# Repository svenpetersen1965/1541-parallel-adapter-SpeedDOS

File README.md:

# 1541-parallel-adapter-SpeedDOS
This is a reliable and easy to build parallel User Port Adapter for the Commodore 1541/1541-II for SpeedDOS

The project consists out of a user port module with a 3D printed case, which also includes a RESET button for the C64. 

There are two different VIA adapters for the 1541 and a low profile one for the narrower sapce in the 1541-II.

BOM Values:
* 1541 Adapter (cable included): 4.91€ (28.06.2020)
* 1541-II Adapter (cable included): 3.30€ (10.12.2020)
* User Port Adapter (no case): 4.65€ (28.06.2020)

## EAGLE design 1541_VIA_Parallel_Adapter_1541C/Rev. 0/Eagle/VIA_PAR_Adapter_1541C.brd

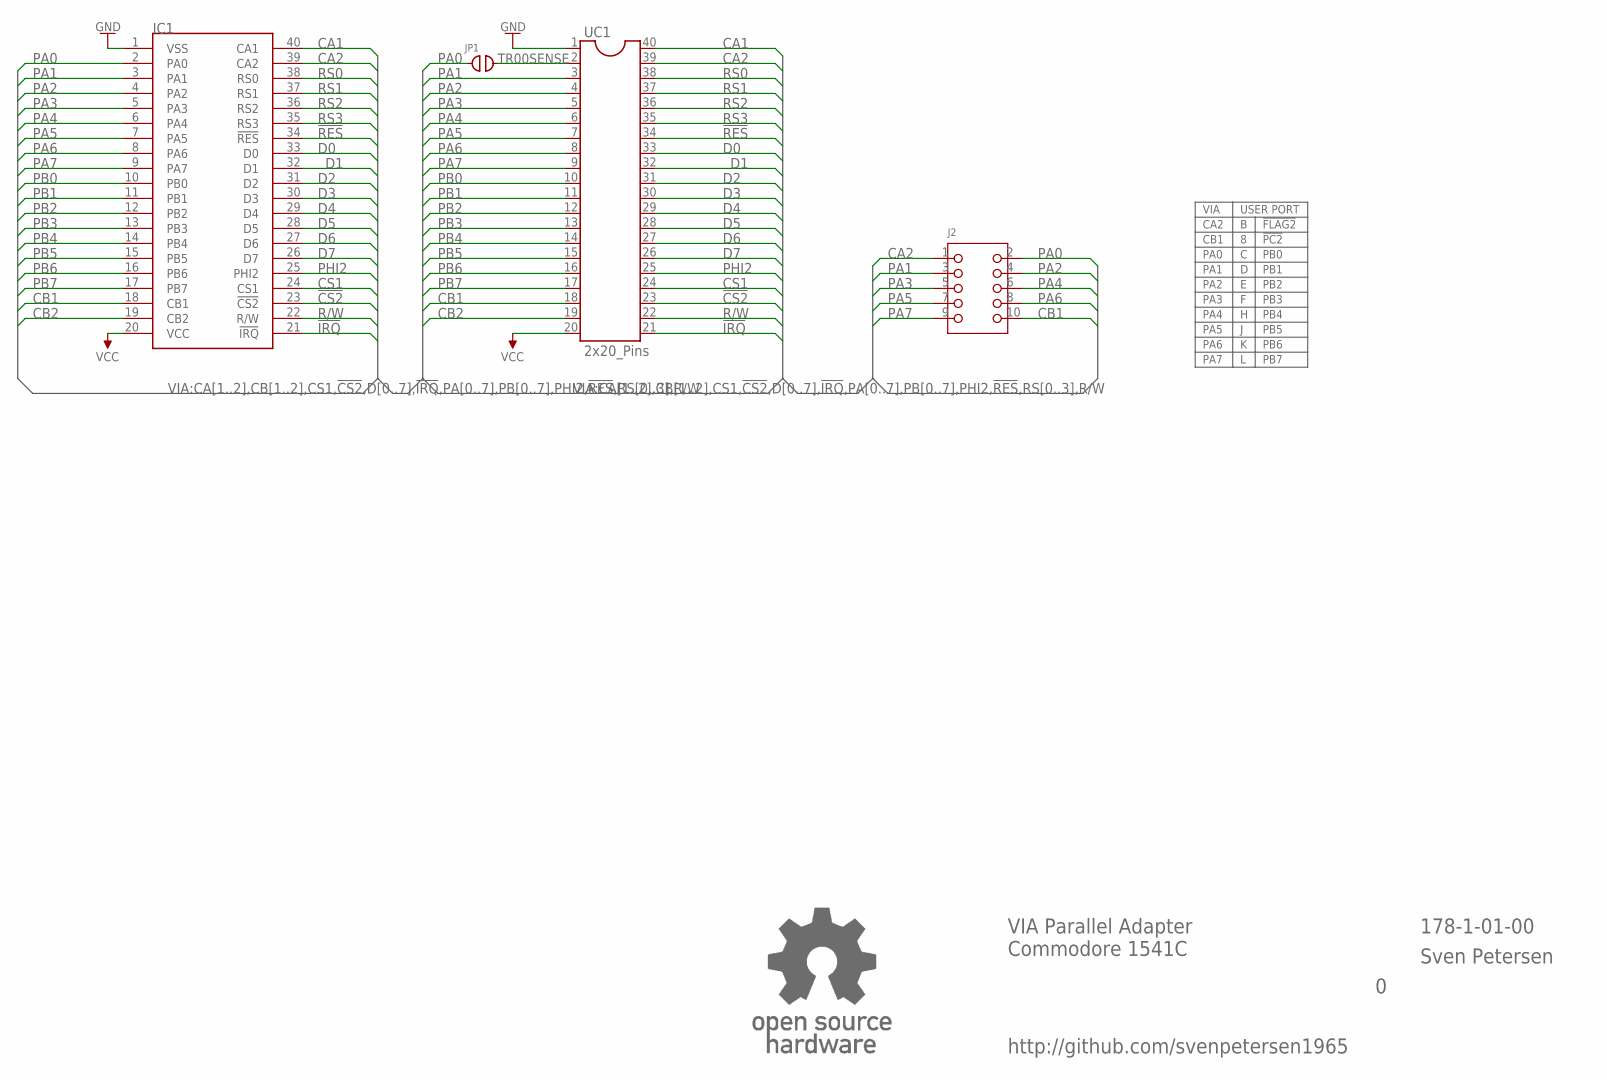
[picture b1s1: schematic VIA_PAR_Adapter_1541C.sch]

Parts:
IC1: MCS6522SOCKET; GS40P
J2: 2X05WV
JP1: COMBI_2P; COMBI-2P
U$10: OPEN_SOURCE_HW; OPENHW
UC1: 2x20_Pins; DIL40_PINS_SS

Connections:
!CS2: IC1.23 (!CS2), UC1.23
!IRQ: IC1.21 (!IRQ), UC1.21
!RES: IC1.34 (!RES), UC1.34
CA1: IC1.40 (CA1), UC1.40
CA2: IC1.39 (CA2), J2.1, UC1.39
CB1: IC1.18 (CB1), J2.10, UC1.18
CB2: IC1.19 (CB2), UC1.19
CS1: IC1.24 (CS1), UC1.24
D0: IC1.33 (D0), UC1.33
D1: IC1.32 (D1), UC1.32
D2: IC1.31 (D2), UC1.31
D3: IC1.30 (D3), UC1.30
D4: IC1.29 (D4), UC1.29
D5: IC1.28 (D5), UC1.28
D6: IC1.27 (D6), UC1.27
D7: IC1.26 (D7), UC1.26
GND: IC1.1 (VSS), UC1.1
PA0: IC1.2 (PA0), J2.2, JP1.1
PA1: IC1.3 (PA1), J2.3, UC1.3
PA2: IC1.4 (PA2), J2.4, UC1.4
PA3: IC1.5 (PA3), J2.5, UC1.5
PA4: IC1.6 (PA4), J2.6, UC1.6
PA5: IC1.7 (PA5), J2.7, UC1.7
PA6: IC1.8 (PA6), J2.8, UC1.8
PA7: IC1.9 (PA7), J2.9, UC1.9
PB0: IC1.10 (PB0), UC1.10
PB1: IC1.11 (PB1), UC1.11
PB2: IC1.12 (PB2), UC1.12
PB3: IC1.13 (PB3), UC1.13
PB4: IC1.14 (PB4), UC1.14
PB5: IC1.15 (PB5), UC1.15
PB6: IC1.16 (PB6), UC1.16
PB7: IC1.17 (PB7), UC1.17
PHI2: IC1.25 (PHI2), UC1.25
R/W: IC1.22 (R/W), UC1.22
RS0: IC1.38 (RS0), UC1.38
RS1: IC1.37 (RS1), UC1.37
RS2: IC1.36 (RS2), UC1.36
RS3: IC1.35 (RS3), UC1.35
TR00SENSE: JP1.2, UC1.2
VCC: IC1.20 (VCC), UC1.20

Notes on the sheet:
VIA
USER PORT
CA2
CB1
PA0
PA1
PA2
PA3
PA4
PA5
PA6
PA7
!FLAG2
!PC2
PB0
PB1
PB2
PB3
PB4
PB5
PB6
PB7
VIA Parallel Adapter Commodore 1541C
Sven Petersen
178-1-01-00
http://github.com/svenpetersen1965

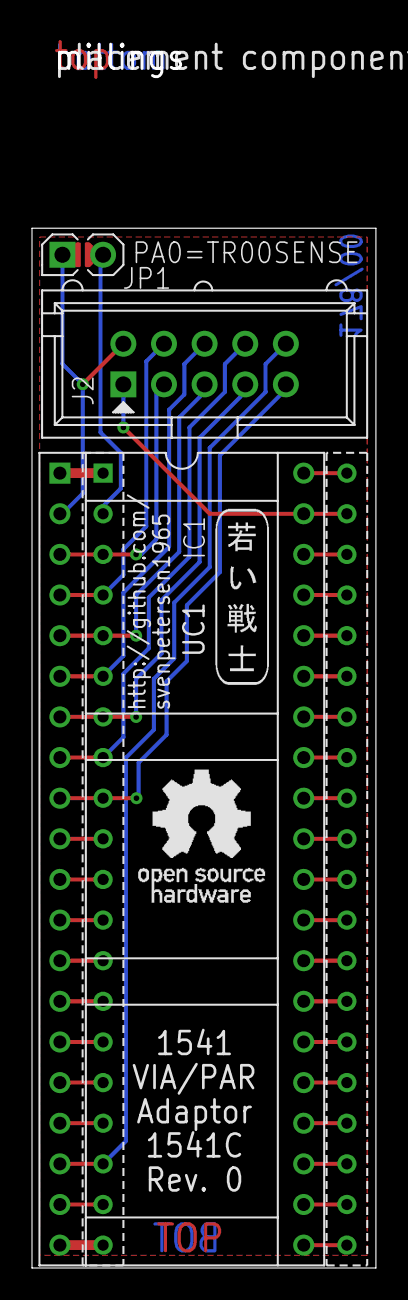
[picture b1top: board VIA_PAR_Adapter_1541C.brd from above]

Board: 2 copper layers, 21.5 x 65.0 mm, 8 parts (0 on the bottom side), 41 nets.

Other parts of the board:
U$6: 2LAYER
U$7: PCB-TITLE/
U$8: SVEN_TAG

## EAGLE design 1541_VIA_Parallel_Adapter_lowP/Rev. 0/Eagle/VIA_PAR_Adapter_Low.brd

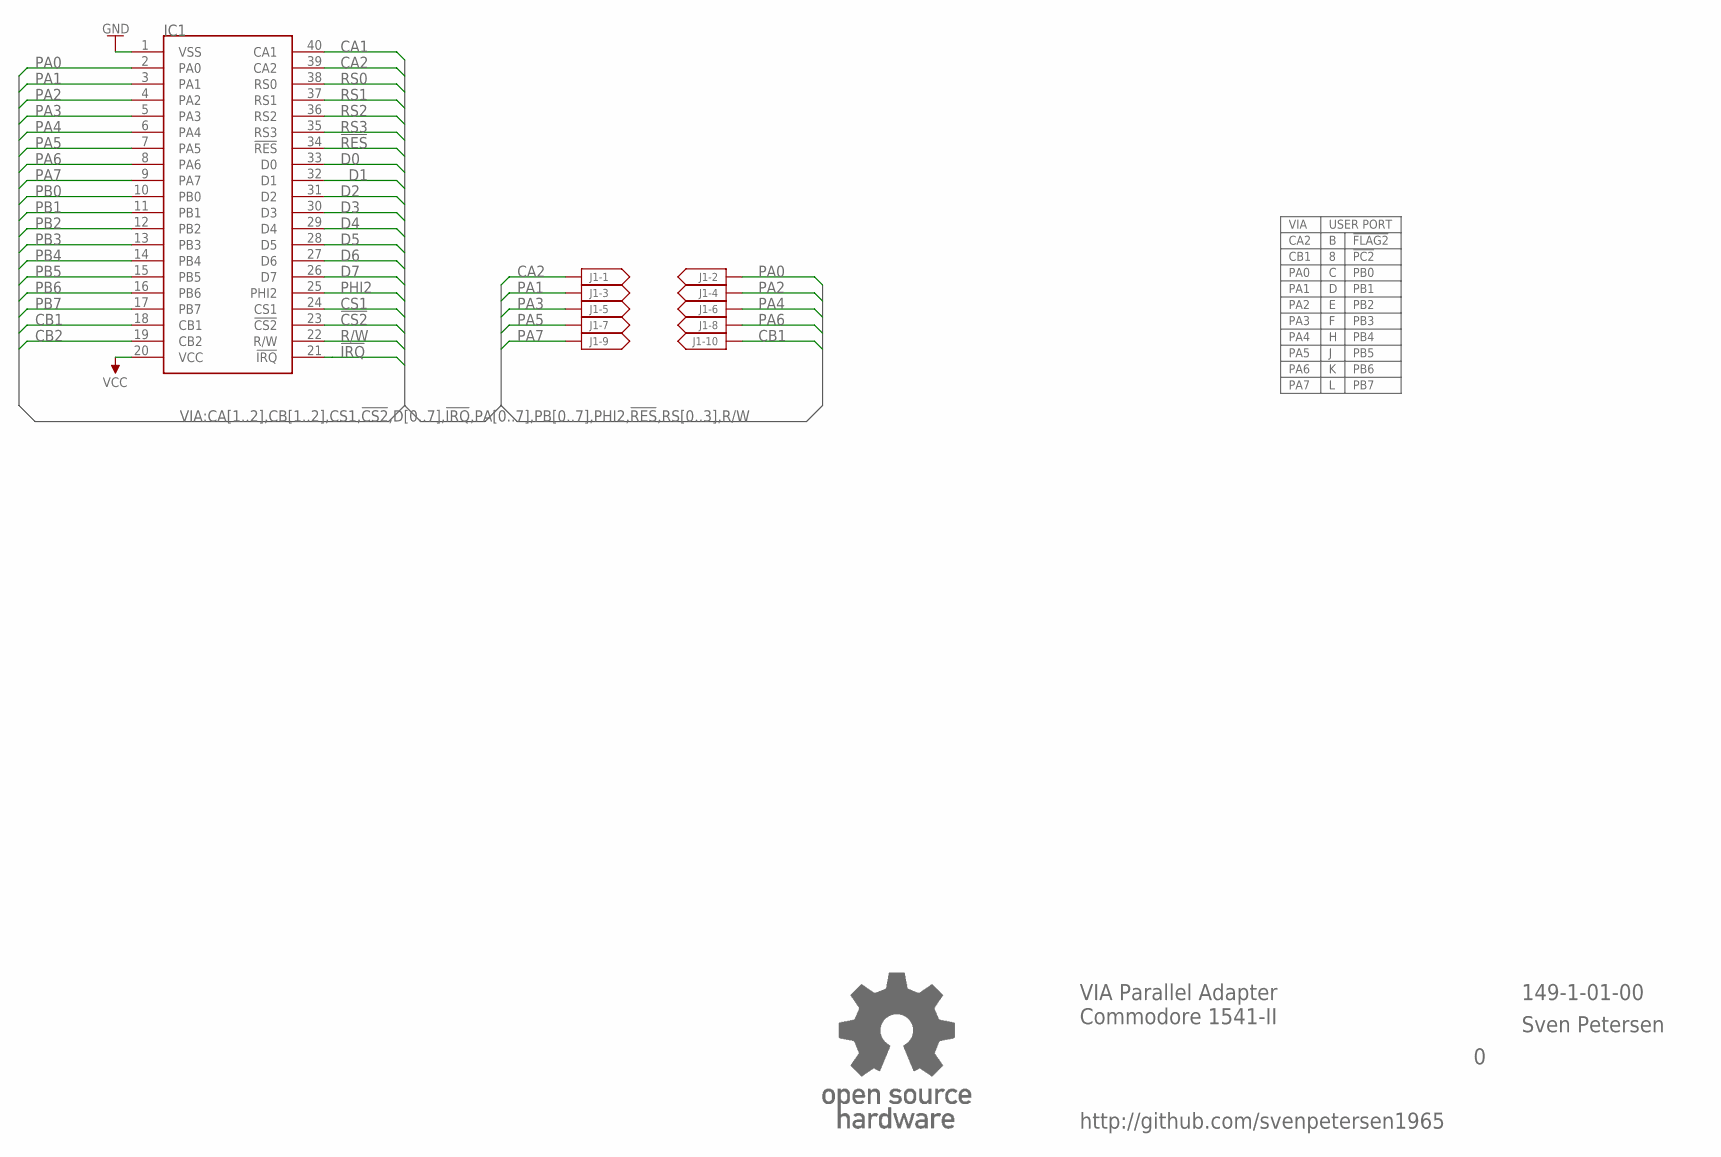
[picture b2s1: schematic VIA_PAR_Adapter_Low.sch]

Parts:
IC1: MCS6522SOPINS; SOCKETPINS40
J1: MICMA10B-THT; MICMA10B
U$5: OPEN_SOURCE_HW; OPENHW

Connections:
!CS2: IC1.23 (!CS2)
!IRQ: IC1.21 (!IRQ)
!RES: IC1.34 (!RES)
CA1: IC1.40 (CA1)
CA2: IC1.39 (CA2), J1.1
CB1: IC1.18 (CB1), J1.10
CB2: IC1.19 (CB2)
CS1: IC1.24 (CS1)
D0: IC1.33 (D0)
D1: IC1.32 (D1)
D2: IC1.31 (D2)
D3: IC1.30 (D3)
D4: IC1.29 (D4)
D5: IC1.28 (D5)
D6: IC1.27 (D6)
D7: IC1.26 (D7)
GND: IC1.1 (VSS)
PA0: IC1.2 (PA0), J1.2
PA1: IC1.3 (PA1), J1.3
PA2: IC1.4 (PA2), J1.4
PA3: IC1.5 (PA3), J1.5
PA4: IC1.6 (PA4), J1.6
PA5: IC1.7 (PA5), J1.7
PA6: IC1.8 (PA6), J1.8
PA7: IC1.9 (PA7), J1.9
PB0: IC1.10 (PB0)
PB1: IC1.11 (PB1)
PB2: IC1.12 (PB2)
PB3: IC1.13 (PB3)
PB4: IC1.14 (PB4)
PB5: IC1.15 (PB5)
PB6: IC1.16 (PB6)
PB7: IC1.17 (PB7)
PHI2: IC1.25 (PHI2)
R/W: IC1.22 (R/W)
RS0: IC1.38 (RS0)
RS1: IC1.37 (RS1)
RS2: IC1.36 (RS2)
RS3: IC1.35 (RS3)
VCC: IC1.20 (VCC)

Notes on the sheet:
VIA
USER PORT
CA2
CB1
PA0
PA1
PA2
PA3
PA4
PA5
PA6
PA7
!FLAG2
!PC2
PB0
PB1
PB2
PB3
PB4
PB5
PB6
PB7
VIA Parallel Adapter Commodore 1541-II
Sven Petersen
149-1-01-00
http://github.com/svenpetersen1965

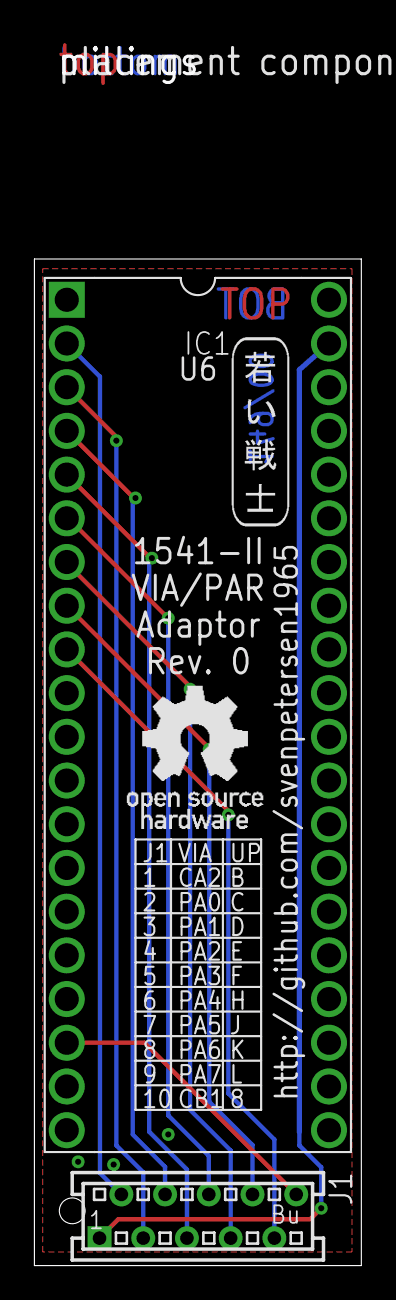
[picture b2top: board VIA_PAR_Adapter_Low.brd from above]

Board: 2 copper layers, 19.0 x 58.5 mm, 6 parts (0 on the bottom side), 10 nets.

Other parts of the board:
U$6: 2LAYER
U$7: PCB-TITLE/
U$8: SVEN_TAG

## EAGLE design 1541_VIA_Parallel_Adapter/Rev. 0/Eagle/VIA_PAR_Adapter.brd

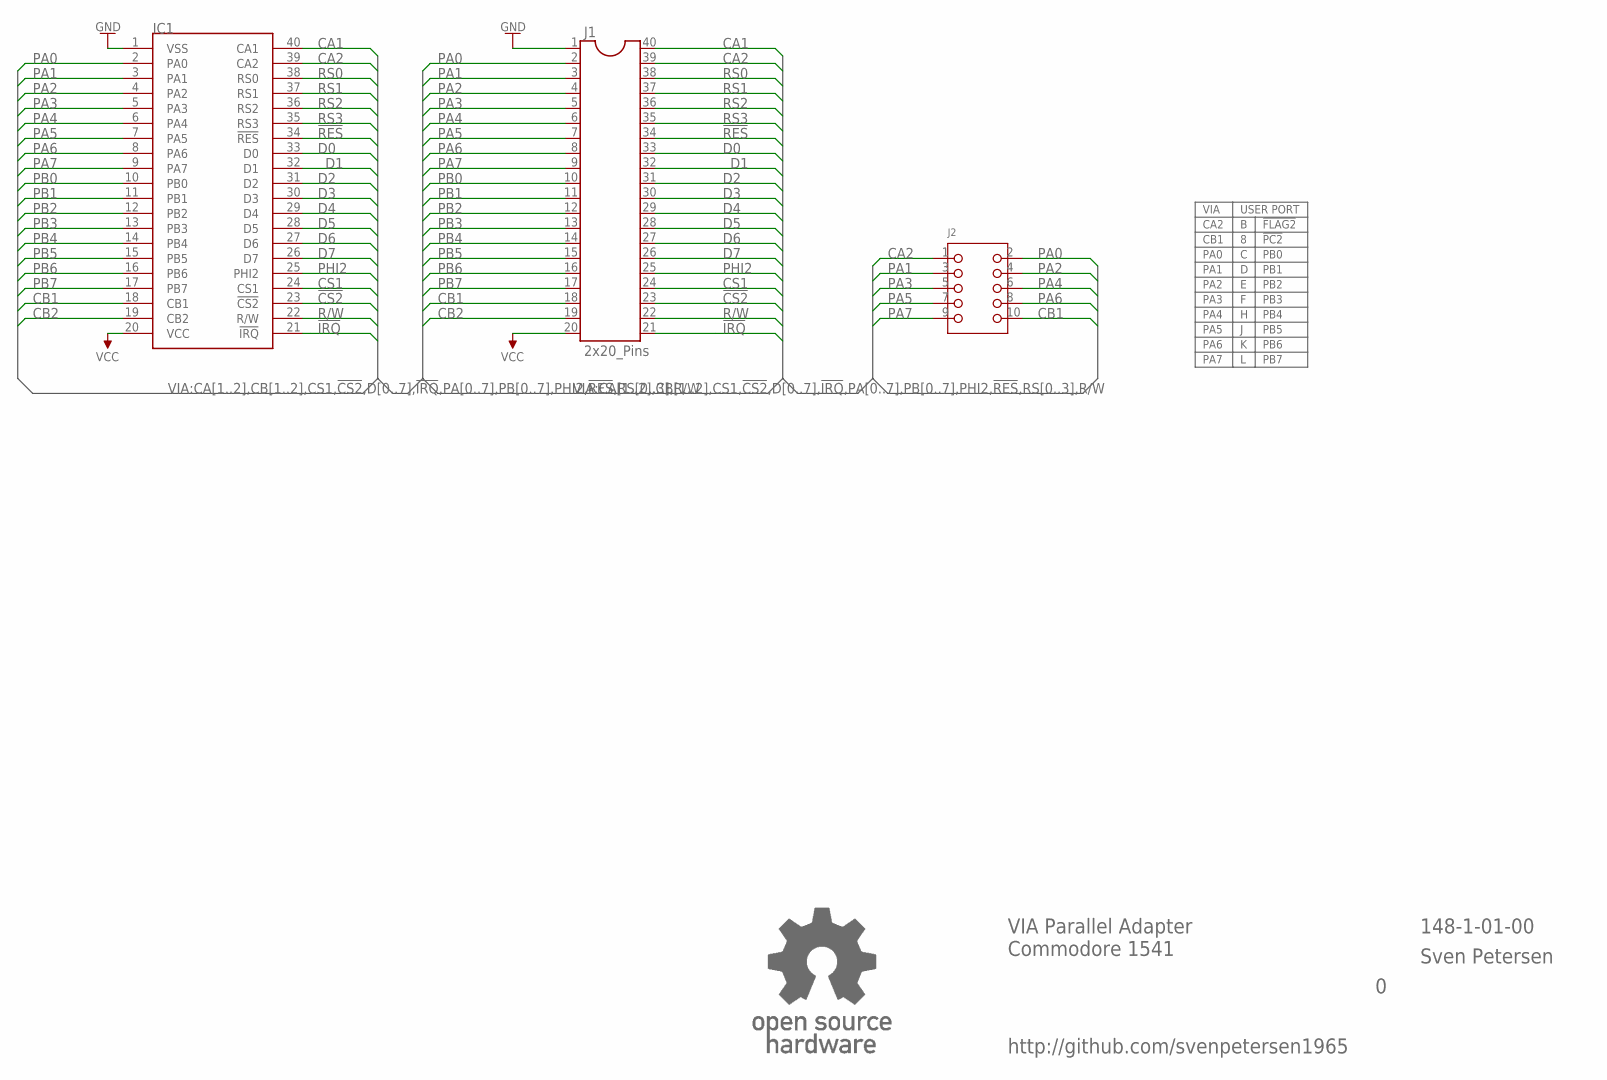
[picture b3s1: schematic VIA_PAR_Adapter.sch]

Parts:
IC1: MCS6522SOCKET; GS40P
J1: 2x20_Pins; DIL40_PINS_SS
J2: 2X05WV
U$10: OPEN_SOURCE_HW; OPENHW

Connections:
!CS2: IC1.23 (!CS2), J1.23
!IRQ: IC1.21 (!IRQ), J1.21
!RES: IC1.34 (!RES), J1.34
CA1: IC1.40 (CA1), J1.40
CA2: IC1.39 (CA2), J1.39, J2.1
CB1: IC1.18 (CB1), J1.18, J2.10
CB2: IC1.19 (CB2), J1.19
CS1: IC1.24 (CS1), J1.24
D0: IC1.33 (D0), J1.33
D1: IC1.32 (D1), J1.32
D2: IC1.31 (D2), J1.31
D3: IC1.30 (D3), J1.30
D4: IC1.29 (D4), J1.29
D5: IC1.28 (D5), J1.28
D6: IC1.27 (D6), J1.27
D7: IC1.26 (D7), J1.26
GND: IC1.1 (VSS), J1.1
PA0: IC1.2 (PA0), J1.2, J2.2
PA1: IC1.3 (PA1), J1.3, J2.3
PA2: IC1.4 (PA2), J1.4, J2.4
PA3: IC1.5 (PA3), J1.5, J2.5
PA4: IC1.6 (PA4), J1.6, J2.6
PA5: IC1.7 (PA5), J1.7, J2.7
PA6: IC1.8 (PA6), J1.8, J2.8
PA7: IC1.9 (PA7), J1.9, J2.9
PB0: IC1.10 (PB0), J1.10
PB1: IC1.11 (PB1), J1.11
PB2: IC1.12 (PB2), J1.12
PB3: IC1.13 (PB3), J1.13
PB4: IC1.14 (PB4), J1.14
PB5: IC1.15 (PB5), J1.15
PB6: IC1.16 (PB6), J1.16
PB7: IC1.17 (PB7), J1.17
PHI2: IC1.25 (PHI2), J1.25
R/W: IC1.22 (R/W), J1.22
RS0: IC1.38 (RS0), J1.38
RS1: IC1.37 (RS1), J1.37
RS2: IC1.36 (RS2), J1.36
RS3: IC1.35 (RS3), J1.35
VCC: IC1.20 (VCC), J1.20

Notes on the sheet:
VIA
USER PORT
CA2
CB1
PA0
PA1
PA2
PA3
PA4
PA5
PA6
PA7
!FLAG2
!PC2
PB0
PB1
PB2
PB3
PB4
PB5
PB6
PB7
VIA Parallel Adapter Commodore 1541
Sven Petersen
148-1-01-00
http://github.com/svenpetersen1965

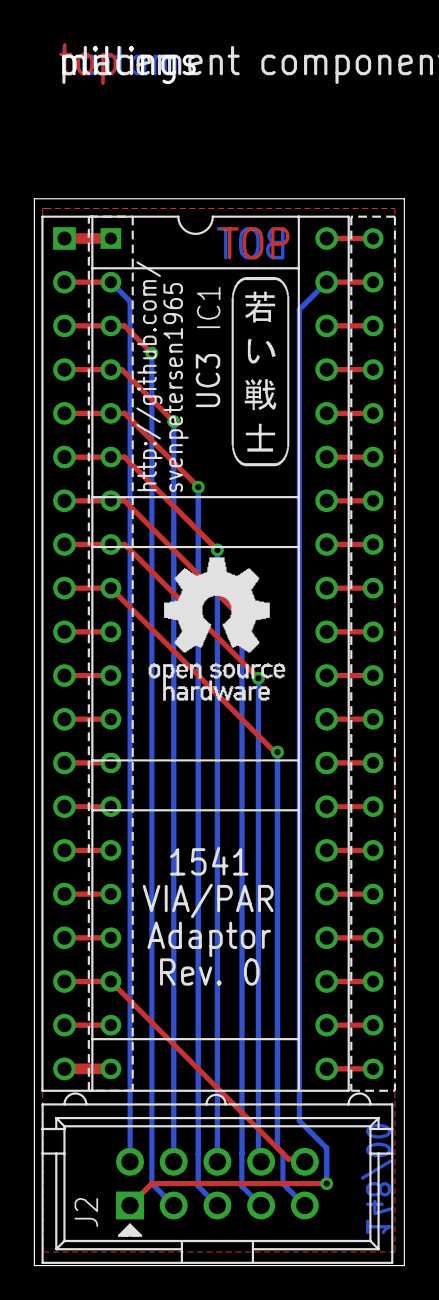
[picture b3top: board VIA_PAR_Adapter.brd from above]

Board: 2 copper layers, 21.5 x 62.0 mm, 7 parts (0 on the bottom side), 40 nets.

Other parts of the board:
U$6: 2LAYER
U$7: PCB-TITLE/
U$8: SVEN_TAG

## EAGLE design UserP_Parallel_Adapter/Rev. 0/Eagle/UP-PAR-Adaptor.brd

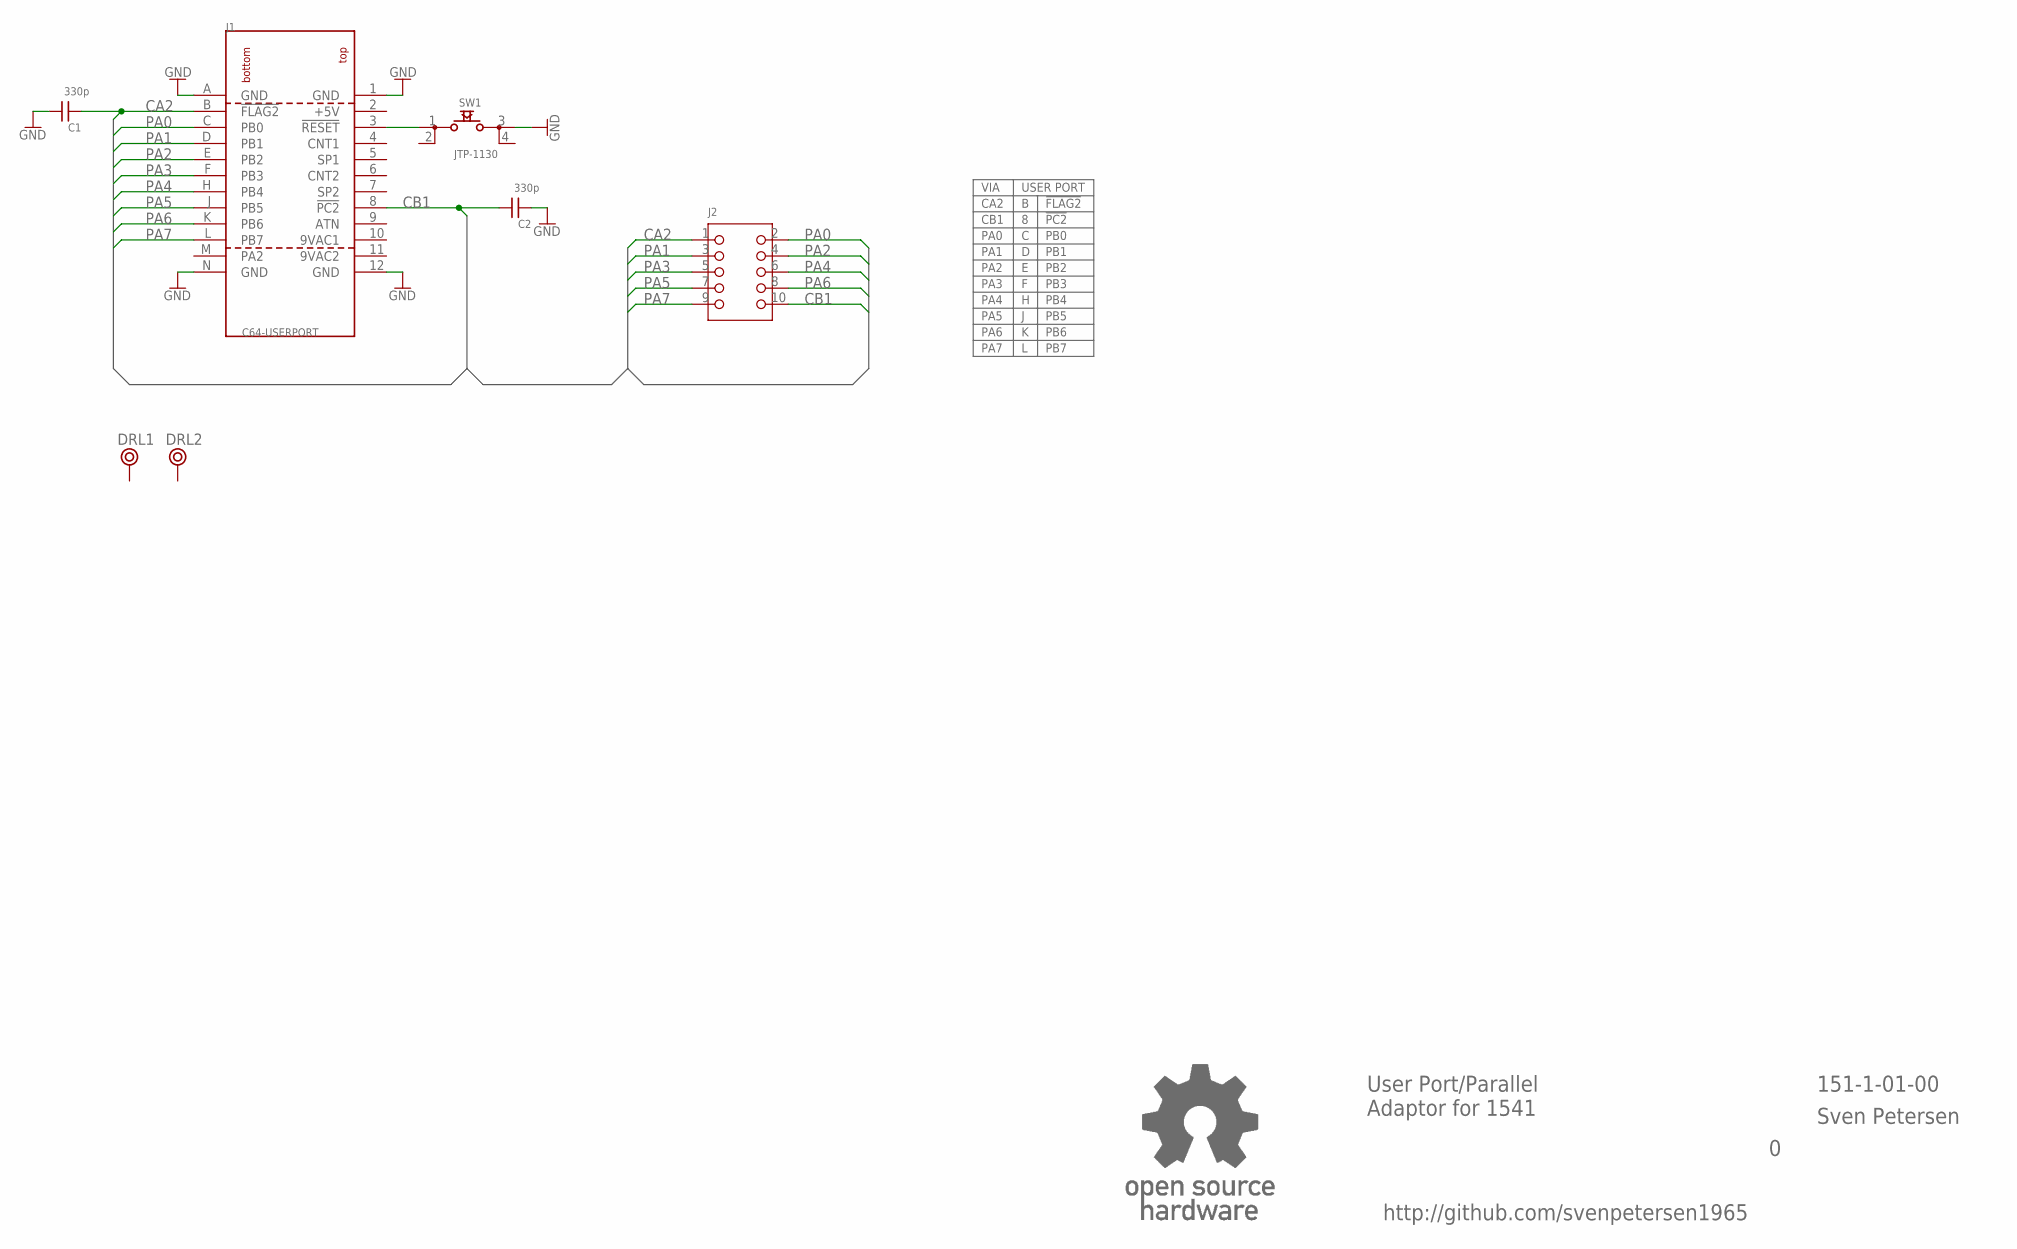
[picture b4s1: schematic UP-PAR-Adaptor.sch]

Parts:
C1, C2: 330p; C-2,5
DRL1, DRL2: BOHR3,5
J1: C64-USERPORT; USERPORT
J2: 2X05WV
SW1: JTP-1130
U$13: OPEN_SOURCE_HW; OPENHW

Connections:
9VAC1: J1.10 (9VAC1)
9VAC2: J1.11 (9VAC2)
+5V: J1.2 (+5V)
CA2: C1.1, J1.B (!FLAG2), J2.1
CB1: C2.2, J1.8 (!PC2), J2.10
GND: C1.2, C2.1, J1.1 (GND), J1.12 (GND), J1.A (GND), J1.N (GND), SW1.3
unnamed: J1.3 (!RESET), SW1.1
PA0: J1.C (PB0), J2.2
PA1: J1.D (PB1), J2.3
PA2: J1.E (PB2), J2.4
PA3: J1.F (PB3), J2.5
PA4: J1.H (PB4), J2.6
PA5: J1.J (PB5), J2.7
PA6: J1.K (PB6), J2.8
PA7: J1.L (PB7), J2.9

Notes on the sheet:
VIA
USER PORT
CA2
CB1
PA0
PA1
PA2
PA3
PA4
PA5
PA6
PA7
!FLAG2
!PC2
PB0
PB1
PB2
PB3
PB4
PB5
PB6
PB7
User Port/Parallel Adaptor for 1541
151-1-01-00
Sven Petersen
http://github.com/svenpetersen1965

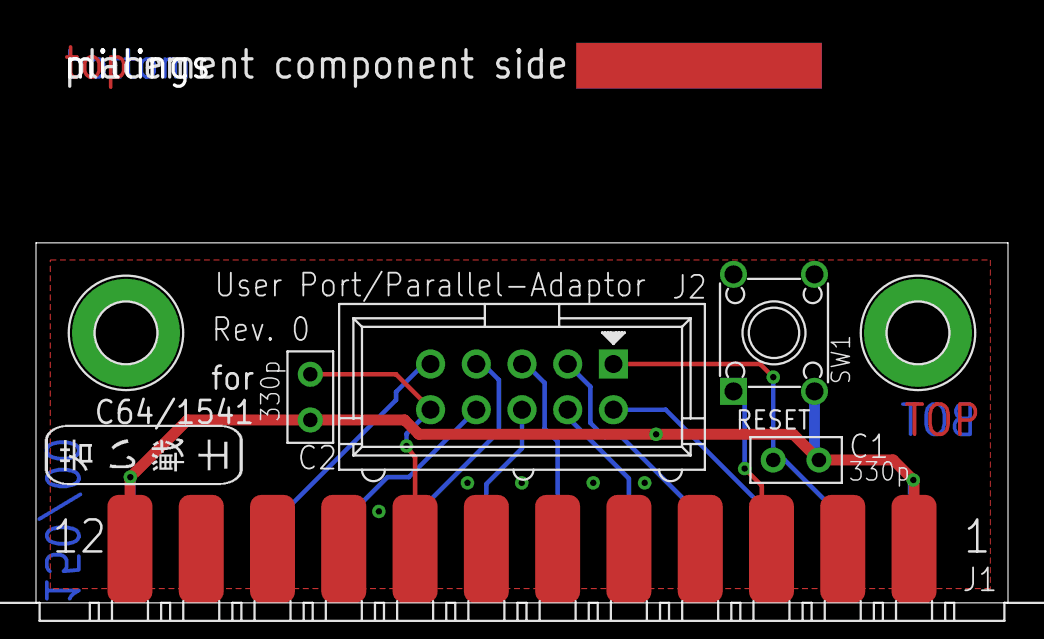
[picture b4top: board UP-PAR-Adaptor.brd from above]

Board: 2 copper layers, 54.0 x 20.0 mm, 11 parts (1 on the bottom side), 12 nets.

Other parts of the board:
U$8: 2LAYER
U$9: PCB-TITLE/
U$10: SVEN_TAG

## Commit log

2020-08-19 Initial release
2020-08-20 Single round pins in BOM
2021-06-03 Adaper board for 1541C released
